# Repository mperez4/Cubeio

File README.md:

# Cubeio
An active meeting engagement tool designed to foster and facilitate decision-making, meaningful dialogue and equal input.

## Getting Started
If this is your first time using the particle, please refer to the [quickstart guide](https://docs.particle.io/quickstart/photon/). The following instructions are written for Mac. If you are using Particle's [web compiler](build.particle.io), search for the `Cubeio` library under libraries. 

### 1. Install [Particle CLI](https://docs.particle.io/tutorials/developer-tools/cli/)

```
$ npm install -g particle-cli
```

### 2. Create a new project

```
$ particle project create
```

### 3. Add library to your project
This should create the library scaffolding necessary to import the library from within your project directory. 

```
$ particle library add Cubeio
```

```
$ particle library view Cubeio
```

## Usage
Once you install the library through the Particle CLI, you should be ready to go.
```c++
#include "Cubeio.h"

Cubeio mycube(D6, D1, A1,A2,A3);
```
Your object declaration might be constructed differently depending on the hardware. Please view the hardware revision and pinouts under `/hardware`.
View the `/examples` and `/src` files to get detailed information about the library.

## Examples
There is a pretty handy script called `upload.sh` inside of every example. `upload.sh` puts the particle device in DFU mode, compiles the cpp file, and uploads the firmware to the device. Make sure that your cube's particle is connected via USB to your computer.
```bash
$ ./examples/set-calibration/upload.sh
```
This script was working well before I upgraded to Catalina... For now, you can use Particle's cloud compiler, which works fine it just takes longer... 

## Hardware
Cubeio uses an Analog Devices [ADXL325](https://www.analog.com/media/en/technical-documentation/data-sheets/ADXL325.pdf) 3-axis accelerometer to calculate the roll and pitch (±5 g) of the cube, a Microchip [MCP73831](http://ww1.microchip.com/downloads/en/DeviceDoc/20001984g.pdf) Li-Polymer charge managment controller, a Worldsemi [WS2812](https://cdn-shop.adafruit.com/datasheets/WS2812.pdf) RGB LED, a single [Schmitt-Trigger](https://datasheet.lcsc.com/szlcsc/ON-Semicon-ON-MC74VHC1G14DTT1G_C242264.pdf) inverter, and a button among other hardware components.
Please view the hardware revision and pinouts under `/hardware`.
You can use this library with any microcontroller if you are using an ADXLxxx chip on its own. You may set the analog pins to your microcontroller and it will work the same. This is intended for the cubeio hardware, so there are no default values set in the `Cubeio object()` object. This library will work for [this](https://www.adafruit.com/product/163?gclid=Cj0KCQiAsdHhBRCwARIsAAhRhsntpFeWXqwBWQDJkoI_y_3HMDCfFyTddMOHF4XVeO5FmmmDFF6SohgaAoF2EALw_wcB) device from Adafruit.

## Contribution
I don't think that the Particle CLI allows branching/merging of libraries from multiple users. This may change, so for now you are welcome to submit pull requests and i will publish the changes.

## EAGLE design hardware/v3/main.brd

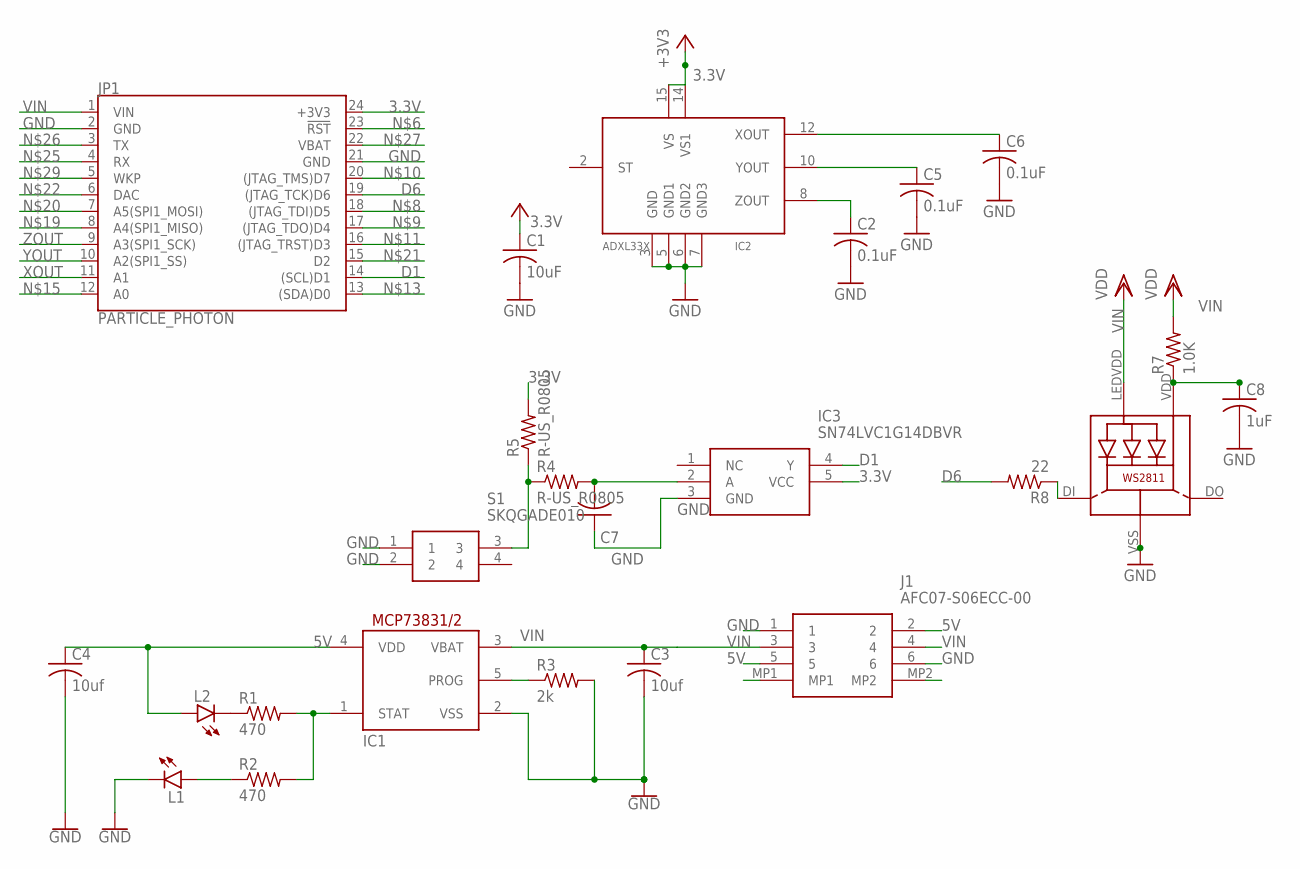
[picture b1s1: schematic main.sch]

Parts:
C1: 10uF; ADAFRUIT_C0805K
C2, C5, C6: 0.1uF; ADAFRUIT_C0805K
C3, C4: 10uf; ADAFRUIT_C0805K
C7: ADAFRUIT_C-USC0805K; ADAFRUIT_C0805K
C8: 1uF; ADAFRUIT_C0805K
IC1: MCP73831/OT; SOT23-5L
IC2: ADXL33X; 16LCSP
IC3: SN74LVC1G14DBVR; SOT95P280X145-5N
J1: AFC07-S06ECC-00; AFC07S06ECC00
JP1: PARTICLE_PHOTON
L1: green; FKIT-LED-1206
L2: blue; FKIT-LED-1206
LED1: WS28115050
R1, R2: 470; R0805
R3: 2k; R0805
R4, R5: R-US_R0805; R0805
R7: 1.0K; R0805
R8: 22; R0805
S1: SKQGADE010; SKQGAKE010

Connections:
3.3V: C1.1, IC2.14 (VS1), IC2.15 (VS), IC3.5 (VCC), JP1.24 (+3V3), R5.2
5V: C4.1, IC1.4 (VDD), J1.2, J1.5, L2.A
D1: IC3.4 (Y), JP1.14 ((SCL)D1)
D6: JP1.19 ((JTAG_TCK)D6), R8.2
GND: C1.2, C2.2, C3.2, C4.2, C5.2, C6.2, C7.1, C8.2, IC1.2 (VSS), IC2.3 (GND), IC2.5 (GND1), IC2.6 (GND2), IC2.7 (GND3), IC3.3 (GND), J1.1, J1.6, JP1.2 (GND), JP1.21 (GND), L1.C, LED1.VSS (GND), R3.2, S1.1, S1.2
IN: C7.2, IC3.2 (A), R4.2
unnamed: IC1.1 (STAT), R1.2, R2.2
unnamed: L2.C, R1.1
unnamed: L1.A, R2.1
unnamed: IC1.5 (PROG), R3.1
unnamed: R4.1, R5.1, S1.3
unnamed: C8.1, LED1.VDD, R7.1
unnamed: LED1.DI, R8.1
VIN: C3.1, IC1.3 (VBAT), J1.3, J1.4, JP1.1 (VIN), LED1.LEDVDD, R7.2
XOUT: C6.1, IC2.12 (XOUT), JP1.11 (A1)
YOUT: C5.1, IC2.10 (YOUT), JP1.10 (A2(SPI1_SS))
ZOUT: C2.1, IC2.8 (ZOUT), JP1.9 (A3(SPI1_SCK))

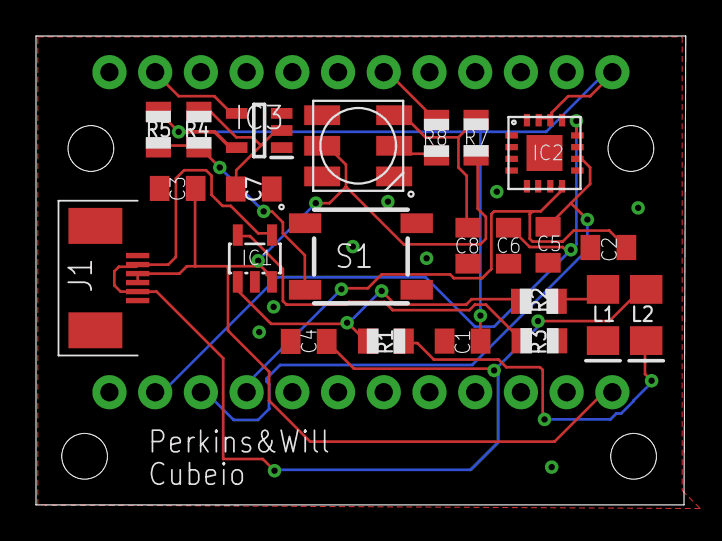
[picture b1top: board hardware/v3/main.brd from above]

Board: 2 copper layers, 36.1 x 26.1 mm, 24 parts (1 on the bottom side), 17 nets.

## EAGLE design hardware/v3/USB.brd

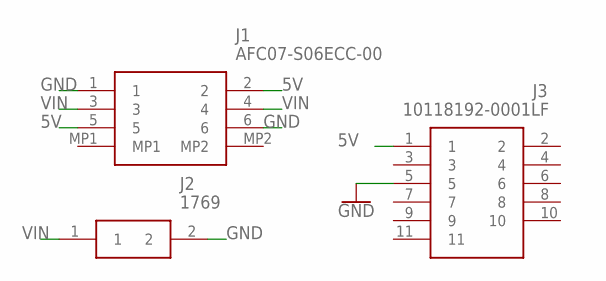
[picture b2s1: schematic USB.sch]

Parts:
J1: AFC07-S06ECC-00; AFC07S06ECC00
J2: 1769
J3: 10118192-0001LF; 101181920001LF

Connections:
5V: J1.2, J1.5, J3.1
GND: J1.1, J1.6, J2.2, J3.5
VIN: J1.3, J1.4, J2.1

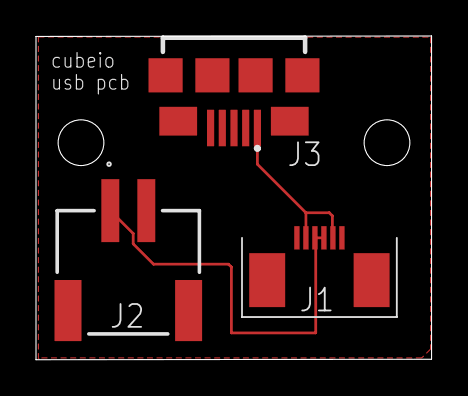
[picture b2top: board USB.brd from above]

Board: 2 copper layers, 22.0 x 18.0 mm, 3 parts (0 on the bottom side), 3 nets.

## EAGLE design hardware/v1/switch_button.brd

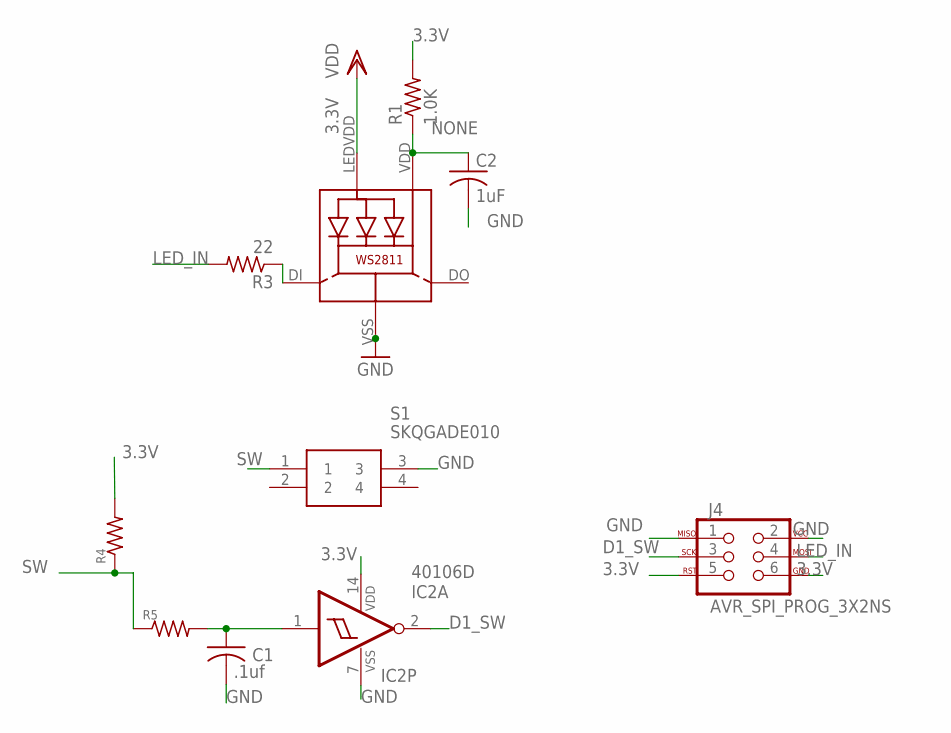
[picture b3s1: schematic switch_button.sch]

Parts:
C1: .1uf; ADAFRUIT_C1206K
C2: 1uF; C1206K
IC2: 40106D; SO14
J4: AVR_SPI_PROG_3X2NS; 2X3-NS
LED1: WS28115050
R1: 1.0K; R1206FAB
R3: 22; M1206
R4, R5: 10k; M1206
S1: SKQGADE010; SKQGAKE010

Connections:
3.3V: IC2.14 (VDD), J4.5, J4.6, LED1.LEDVDD, R1.2, R4.2
D1_SW: IC2.2 (O), J4.3
GND: C1.2, C2.2, IC2.7 (VSS), J4.1, J4.2, LED1.VSS (GND), S1.3
LED_IN: J4.4, R3.2
unnamed: LED1.DI, R3.1
unnamed: C1.1, IC2.1 (I), R5.2
NONE: C2.1, LED1.VDD, R1.1
SW: R4.1, R5.1, S1.1

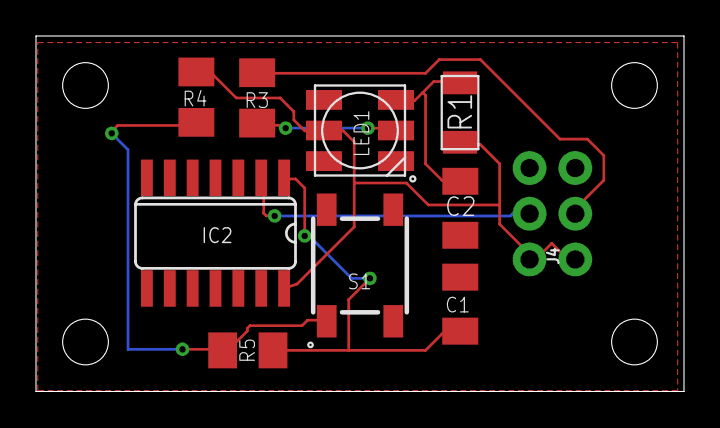
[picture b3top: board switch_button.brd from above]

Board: 2 copper layers, 36.0 x 19.8 mm, 10 parts (0 on the bottom side), 8 nets.

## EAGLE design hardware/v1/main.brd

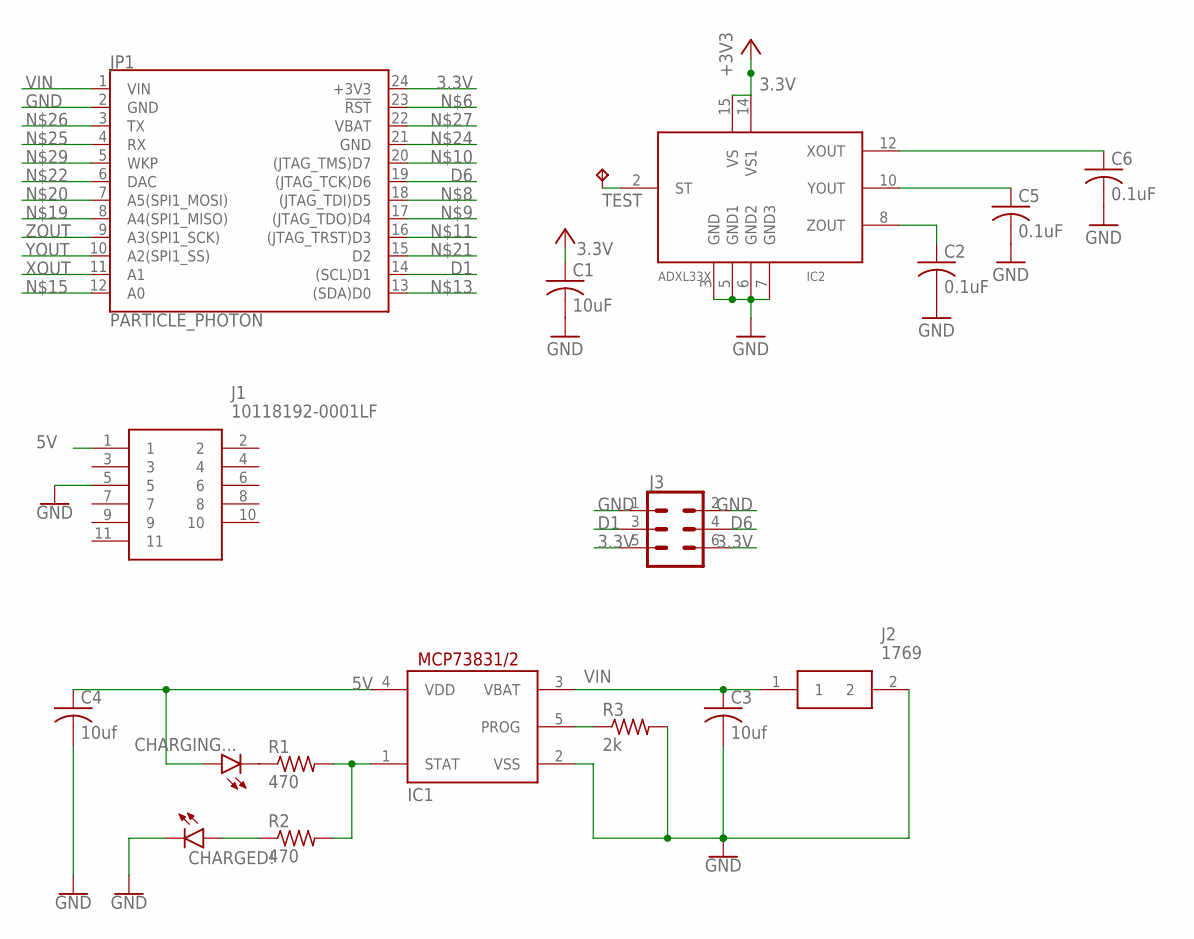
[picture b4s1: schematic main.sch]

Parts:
C1: 10uF; ADAFRUIT_C1206K
C2, C5, C6: 0.1uF; ADAFRUIT_C1206K
C3, C4: 10uf; C1206K
CHARGED!: green; FKIT-LED-1206
CHARGING...: blue; FKIT-LED-1206
IC1: MCP73831/OT; SOT23-5L
IC2: ADXL33X; 16LCSP
J1: 10118192-0001LF; 101181920001LF
J2: 1769
J3: CONN_03X2FEMALE_SMD; 2X3_SMD
JP1: PARTICLE_PHOTON
R1, R2: 470; M1206
R3: 2k; M1206
TEST: TPTP14R; TP14R

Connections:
3.3V: C1.1, IC2.14 (VS1), IC2.15 (VS), J3.5, J3.6, JP1.24 (+3V3)
5V: C4.1, CHARGING....A, IC1.4 (VDD), J1.1
D1: J3.3, JP1.14 ((SCL)D1)
D6: J3.4, JP1.19 ((JTAG_TCK)D6)
GND: C1.2, C2.2, C3.2, C4.2, C5.2, C6.2, CHARGED!.C, IC1.2 (VSS), IC2.3 (GND), IC2.5 (GND1), IC2.6 (GND2), IC2.7 (GND3), J1.5, J2.2, J3.1, J3.2, JP1.2 (GND), R3.2
unnamed: IC1.1 (STAT), R1.2, R2.2
unnamed: CHARGING....C, R1.1
unnamed: CHARGED!.A, R2.1
unnamed: IC1.5 (PROG), R3.1
TEST: IC2.2 (ST), TEST.TP
VIN: C3.1, IC1.3 (VBAT), J2.1, JP1.1 (VIN)
XOUT: C6.1, IC2.12 (XOUT), JP1.11 (A1)
YOUT: C5.1, IC2.10 (YOUT), JP1.10 (A2(SPI1_SS))
ZOUT: C2.1, IC2.8 (ZOUT), JP1.9 (A3(SPI1_SCK))

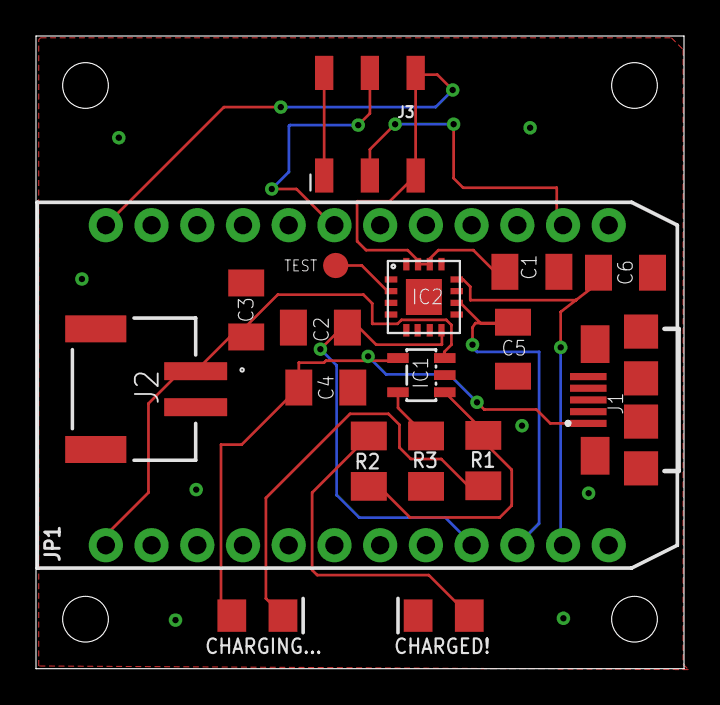
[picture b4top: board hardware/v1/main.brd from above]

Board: 2 copper layers, 36.0 x 35.1 mm, 18 parts (0 on the bottom side), 14 nets.

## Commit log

2019-10-22 remove default readme
2019-10-22 removed files
2019-10-23 external led working.
2019-10-23 added brighness on external led
2019-10-23 ignoring more junk
2019-10-23 updated example
2019-10-23 added button functionality
2019-10-25 updated some variables and changed function
2019-10-28 error handling
2019-10-28 saving values locally, then to EEPROM
2019-10-29 getting close to saving to EEPROM
2019-10-29 support for eeprom
2019-10-29 new example basic mode select
2019-10-30 fully working
2019-10-30 reading successfully from EEPROM to set default calibration values
2019-10-30 upload script
2019-10-30 working mode select example
2019-10-30 button working
2019-10-30 unused var...
2019-10-30 added upload and rename
2019-10-30 printing calibration results
2019-10-31 need to debounce the registration
2019-10-31 fixed active side bug
2019-10-31 updated compiles
2019-11-06 added publishOnChange
2019-11-06 working publish on change
2019-11-06 notes
2019-11-06 ignoring .swp
2019-11-06 renamed getrollpitch to calculaterollpitch
2019-11-06 added media for readme
2019-11-06 new pics
2019-11-06 added firmware scaffolding. Working with web compiler
2019-11-06 updated cal results
2019-11-06 updated code to support new lib
2019-11-06 deleted
2019-11-07 added eagle files
2019-11-07 removed sh files
2019-11-07 ignoring compile scripts in examples
2019-11-07 added scripts
2019-12-05 added v3 hardware files

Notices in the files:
parts and their libraries:
SparkFun-LED: Licensing: Creative Commons ShareAlike 4.0 International - https://creativecommons.org/licenses/by-sa/4.0
microbuilder: This work is placed in the public domain, and may be freely used for commercial and non-commercial work with the following conditions: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
